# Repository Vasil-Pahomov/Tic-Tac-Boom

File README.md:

# Tic-Tac-Boom
Аппаратная реализация игры Тик Так Бумм. Дополнительно реализован таймер на 1 минуту, полезный в некоторых играх, например "Скажи иначе" (Alias)

# Использование
Короткое нажатие кнопки запускает таймер, длинное - "бомбу" для Тик Так Бумм.

# Схема

# Компоненты
## Контроллер
В проекте использована "китайская" плата Arduino Pro Mini, переведённая в режим тактирования от внутреннего RC-генератора (отличная статья: https://tsibrov.blogspot.com/2018/12/arduino-internal-rc.html). Из платы нужно выпаять стабилизатор напряжения и светодиод питания (https://alexgyver.ru/lessons/power-sleep/)
Можно просто выпаять стабилизатор и светодиод, но тогда в режиме ожидания аккумулятор будет выжираться гораздо быстрее.

## Экран
Широко распространённый OLED-экран 1.3 дюйма 128x64 точки с интерфейсом SPI.

## Плата защиты/заряда аккумулятора
"Народная" плата на TP4056

## Плата повышающего преобразователя напряжения до 5V
Лежала в старых запасах. Из платы пришлось выпаять разъём USB и подрезать её. Сейчас есть более миниатюрные варианты, можно использовать их.

## Кнопка, динамик, остальные элементы
Могут быть любыми. Кнопку лучше искать со встроенным светодиодом - выгдядит эффектнее

# Конструкция
Корпус сделал из двух половинок - каждая из отрезанной от пластиковой бутылки части. Внутри жёсткий каркас образуют круглая плата и вставленный перпендикулярно круг из 3мм оргстекла с вырезами под кнопку и динамик. Кнопка вклеена в каркас, т.к. корпус слишком мягкий и проседал бы при нажатиях.
Не могу сказать, что очень удачная, поэтому не буду рекомендовать к повторению. Проект kicad со схемой и печатной платой есть в папке kicad, можно взять на за основу.

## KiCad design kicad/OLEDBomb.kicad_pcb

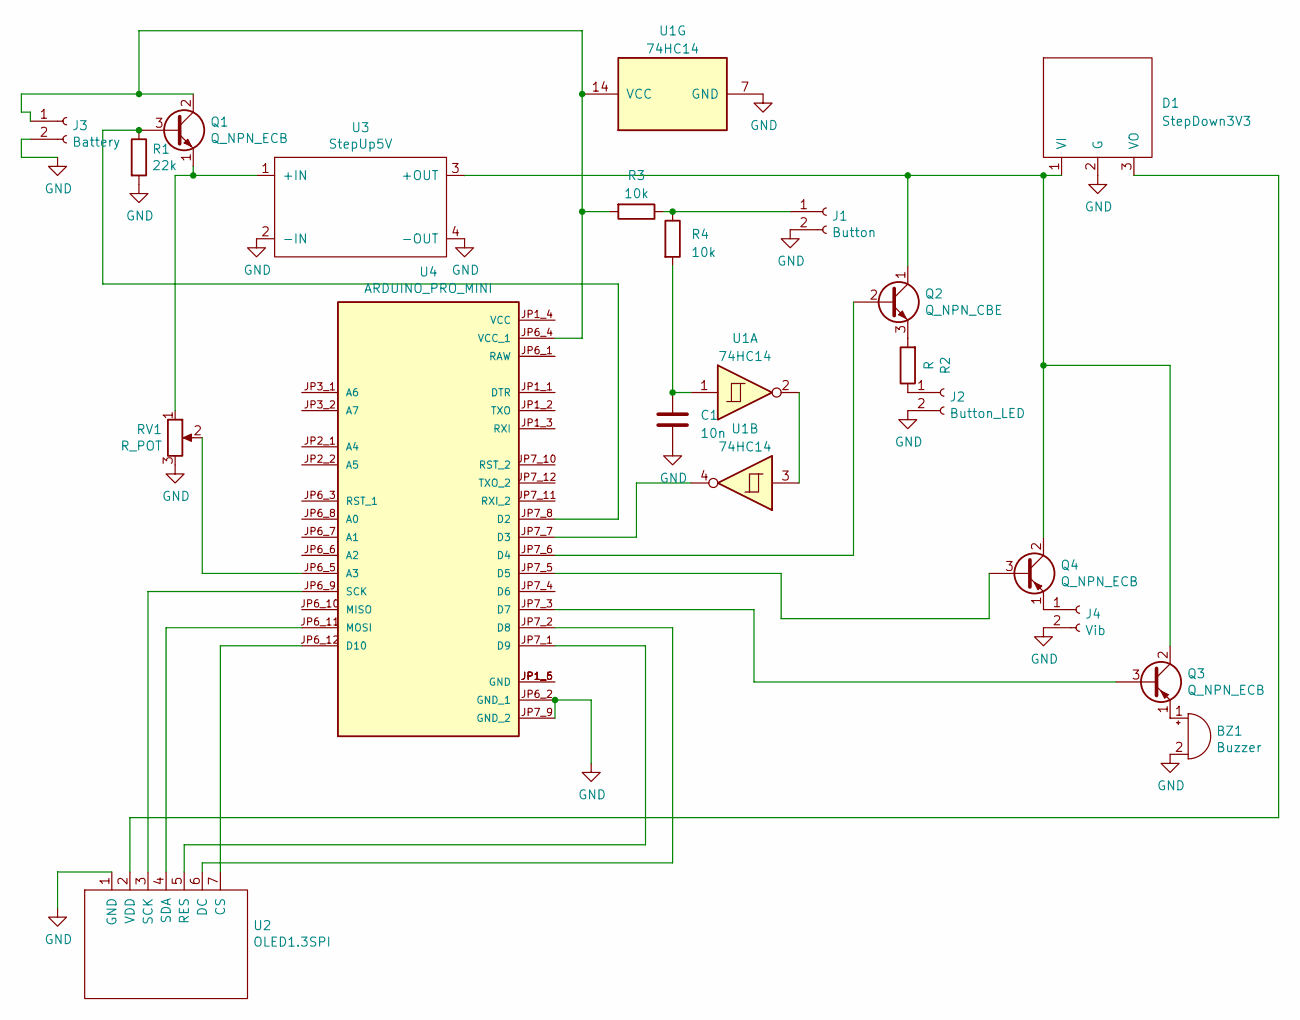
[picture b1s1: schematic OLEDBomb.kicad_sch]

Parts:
BZ1: Buzzer; TestPoint_2Pads_Pitch2.54mm_Drill0.8mm
C1: 10n; C_1206_3216Metric
D1: StepDown3V3
J1: Button; TestPoint_2Pads_Pitch2.54mm_Drill0.8mm
J2: Button_LED; TestPoint_2Pads_Pitch2.54mm_Drill0.8mm
J3: Battery; TestPoint_2Pads_Pitch5.08mm_Drill1.3mm
J4: Vib; TestPoint_2Pads_Pitch2.54mm_Drill0.8mm
Q1: Q_NPN_ECB; TO-220F-3_Vertical
Q2: Q_NPN_CBE; TO-92
Q3, Q4: Q_NPN_ECB; TO-220-3_Vertical
R1: 22k; R_0805_2012Metric_Pad1.20x1.40mm_HandSolder
R2: R; R_Axial_DIN0207_L6.3mm_D2.5mm_P10.16mm_Horizontal
R3, R4: 10k; R_0805_2012Metric_Pad1.20x1.40mm_HandSolder
RV1: R_POT; Potentiometer_Bourns_3386C_Horizontal
U1: 74HC14
U2: OLED1.3SPI; PinHeader_1x07_P2.54mm_Vertical
U3: StepUp5V
U4: ARDUINO_PRO_MINI; MODULE_ARDUINO_PRO_MINI_NO_PROG_PING; PARTREV N/A

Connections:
GND: BZ1.2 (+), C1.1, D1.2 (G), J1.2, J2.2, J3.2, J4.2, R1.2, RV1.3, U1.7 (GND), U2.1 (GND), U3.2 (-IN), U3.4 (-OUT), U4.JP6_2 (GND_1), U4.JP7_9 (GND_2)
unnamed: BZ1.1 (-), Q3.1 (E)
unnamed: C1.2, R4.2, U1.1
unnamed: D1.1 (VI), Q2.1 (C), Q3.2 (C), Q4.2 (C), U3.3 (+OUT)
unnamed: D1.3 (VO), U2.2 (VDD)
unnamed: J1.1, R3.1, R4.1
unnamed: J2.1, R2.1
unnamed: J3.1, Q1.2 (C), R3.2, U1.14 (VCC), U4.JP6_4 (VCC_1)
unnamed: J4.1, Q4.1 (E)
unnamed: Q1.3 (B), R1.1, U4.JP7_8 (D2)
unnamed: Q1.1 (E), RV1.1, U3.1 (+IN)
unnamed: Q2.2 (B), U4.JP7_6 (D4)
unnamed: Q2.3 (E), R2.2
unnamed: Q3.3 (B), U4.JP7_3 (D7)
unnamed: Q4.3 (B), U4.JP7_5 (D5)
unnamed: U1.2, U1.3
unnamed: U2.7 (CS), U4.JP6_12 (D10)
unnamed: U2.6 (DC), U4.JP7_2 (D8)
unnamed: U2.5 (RES), U4.JP7_1 (D9)
unnamed: U2.3 (SCK), U4.JP6_9 (SCK)
unnamed: U2.4 (SDA), U4.JP6_11 (MOSI)
unnamed: RV1.2, U4.JP6_5 (A3)
unnamed: U1.4, U4.JP7_7 (D3)

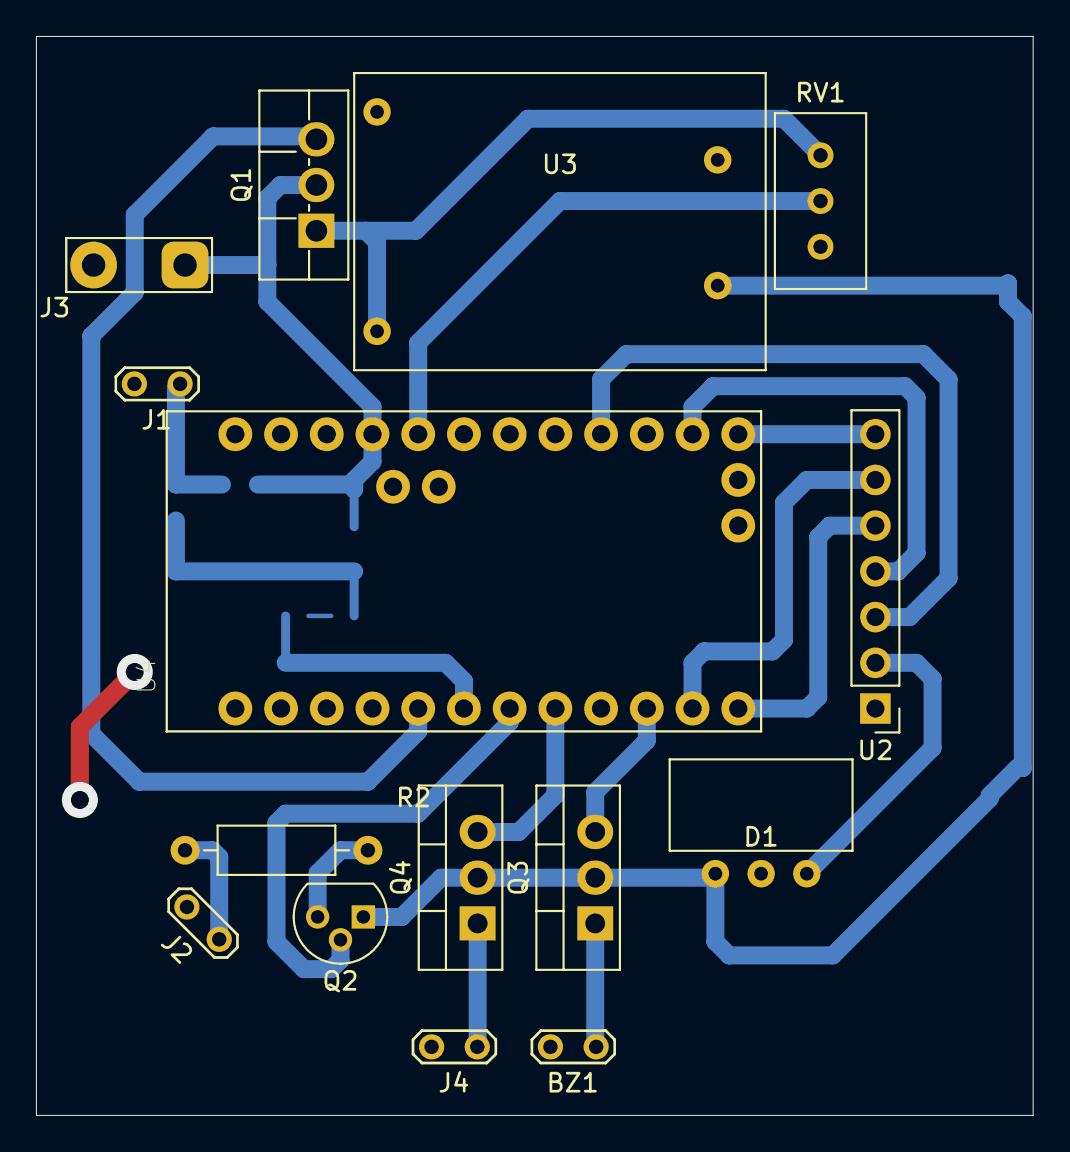
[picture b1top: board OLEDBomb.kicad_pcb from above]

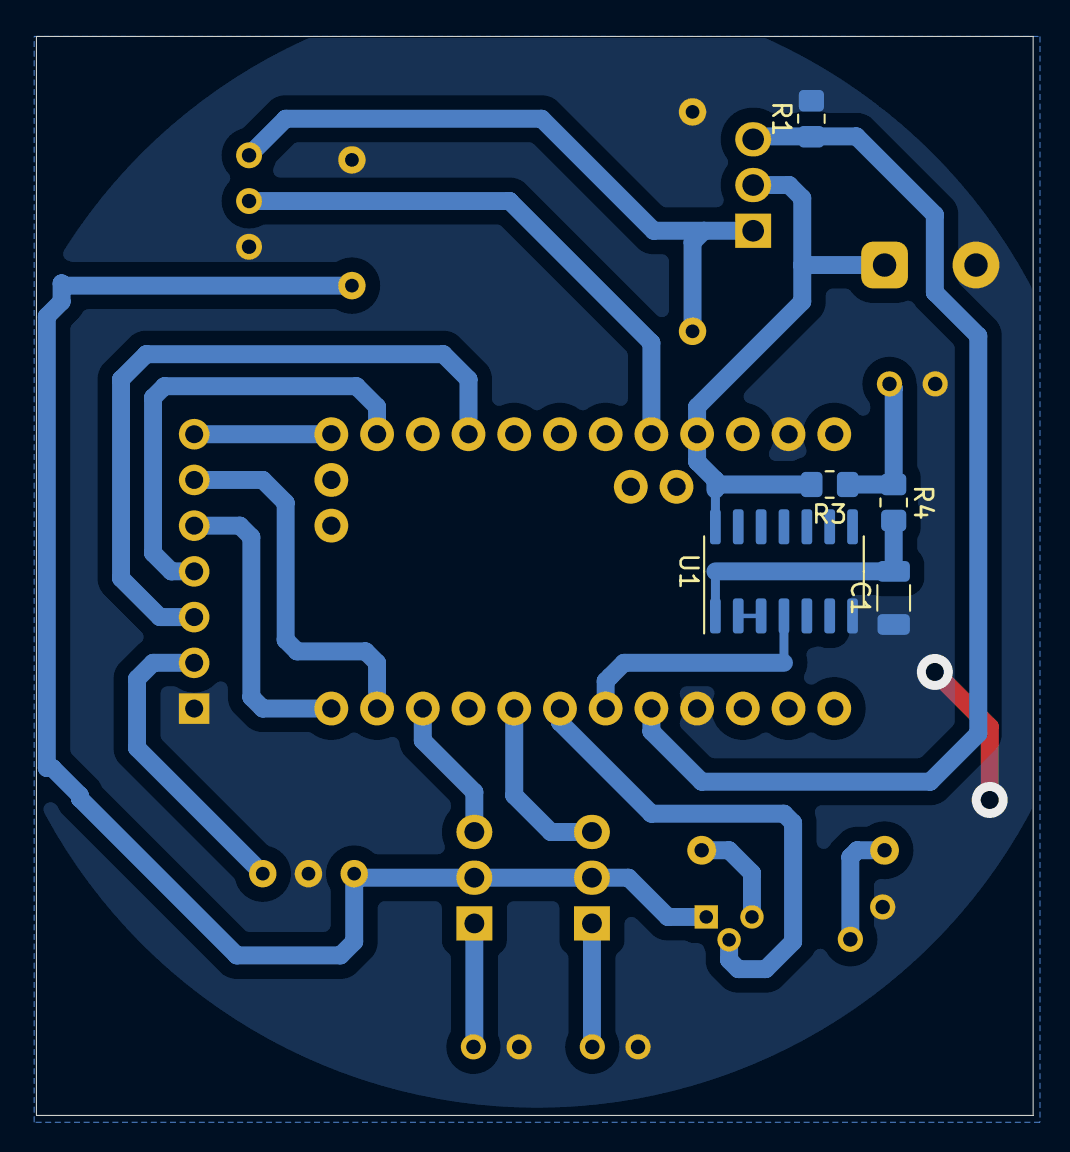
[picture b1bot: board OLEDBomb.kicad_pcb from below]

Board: 2 copper layers, 55.4 x 59.9 mm, 20 parts (5 on the bottom side), 23 nets.

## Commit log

2022-02-09 overview picture
2022-02-09 Pictures
2022-08-27 Locking/unlocking by triple button press
2023-06-07 Added English syllables Added ability to remove syllable limitations (no ellipses and the beginning and/or end of syllables) Added settings (hold the button): rus/eng syllables for bomb, small/big te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
2023-06-08 Missing Kicad files
2023-06-08 Added feature that prevents the same syllable from appearing too frequently
2023-06-08 minor fixes
2023-09-17 Added Belarussian language
2024-02-10 Improve button handling
